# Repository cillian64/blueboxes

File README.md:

# blueboxes
Exciting bass guitar orientated DIY effects pedals

## DI
* DI box for practice with headphones or a consumer hi-fi amp
* Inputs:
    * Unbalanced mono Hi-Z from guitar (TS)
    * Unbalanced stereo line-level backing (TRS)
* Outputs:
    * Unbalanced stereo line-level to amp (RCA)
    * Unbalanced stereo headphone-level (TRS)
* Controls:
    * Instrument volume (mono logpot)
    * Output volume (stereo logpot)
    * on/off switch
* Inside:
    * Hi-Z opamp with gain control for instrument
    * dual op-amp buffer on instrument
    * summing network into stereo opamp outputs

## DSP
* Platform for custom DSP effects
* Inputs:
    * Unbalanced mono hi-Z from guitar (TS)
* Outputs:
    * Unbalanced mono (TS)
* Controls:
    * Rotary encoder with push
    * 4-digit 7-seg LED
    * Stomp-switch for on/thru

## Silly Fuzz
* Simple silicon clone of Fuzz-Face
* Inputs:
    * Unbalanced mono hi-Z from guitar (TS)
* Outputs:
    * Unbalanced mono (TS)
* Controls:
    * Stomp-switch for on/thru
    * Volume log-pot
    * Fuzz-level pot

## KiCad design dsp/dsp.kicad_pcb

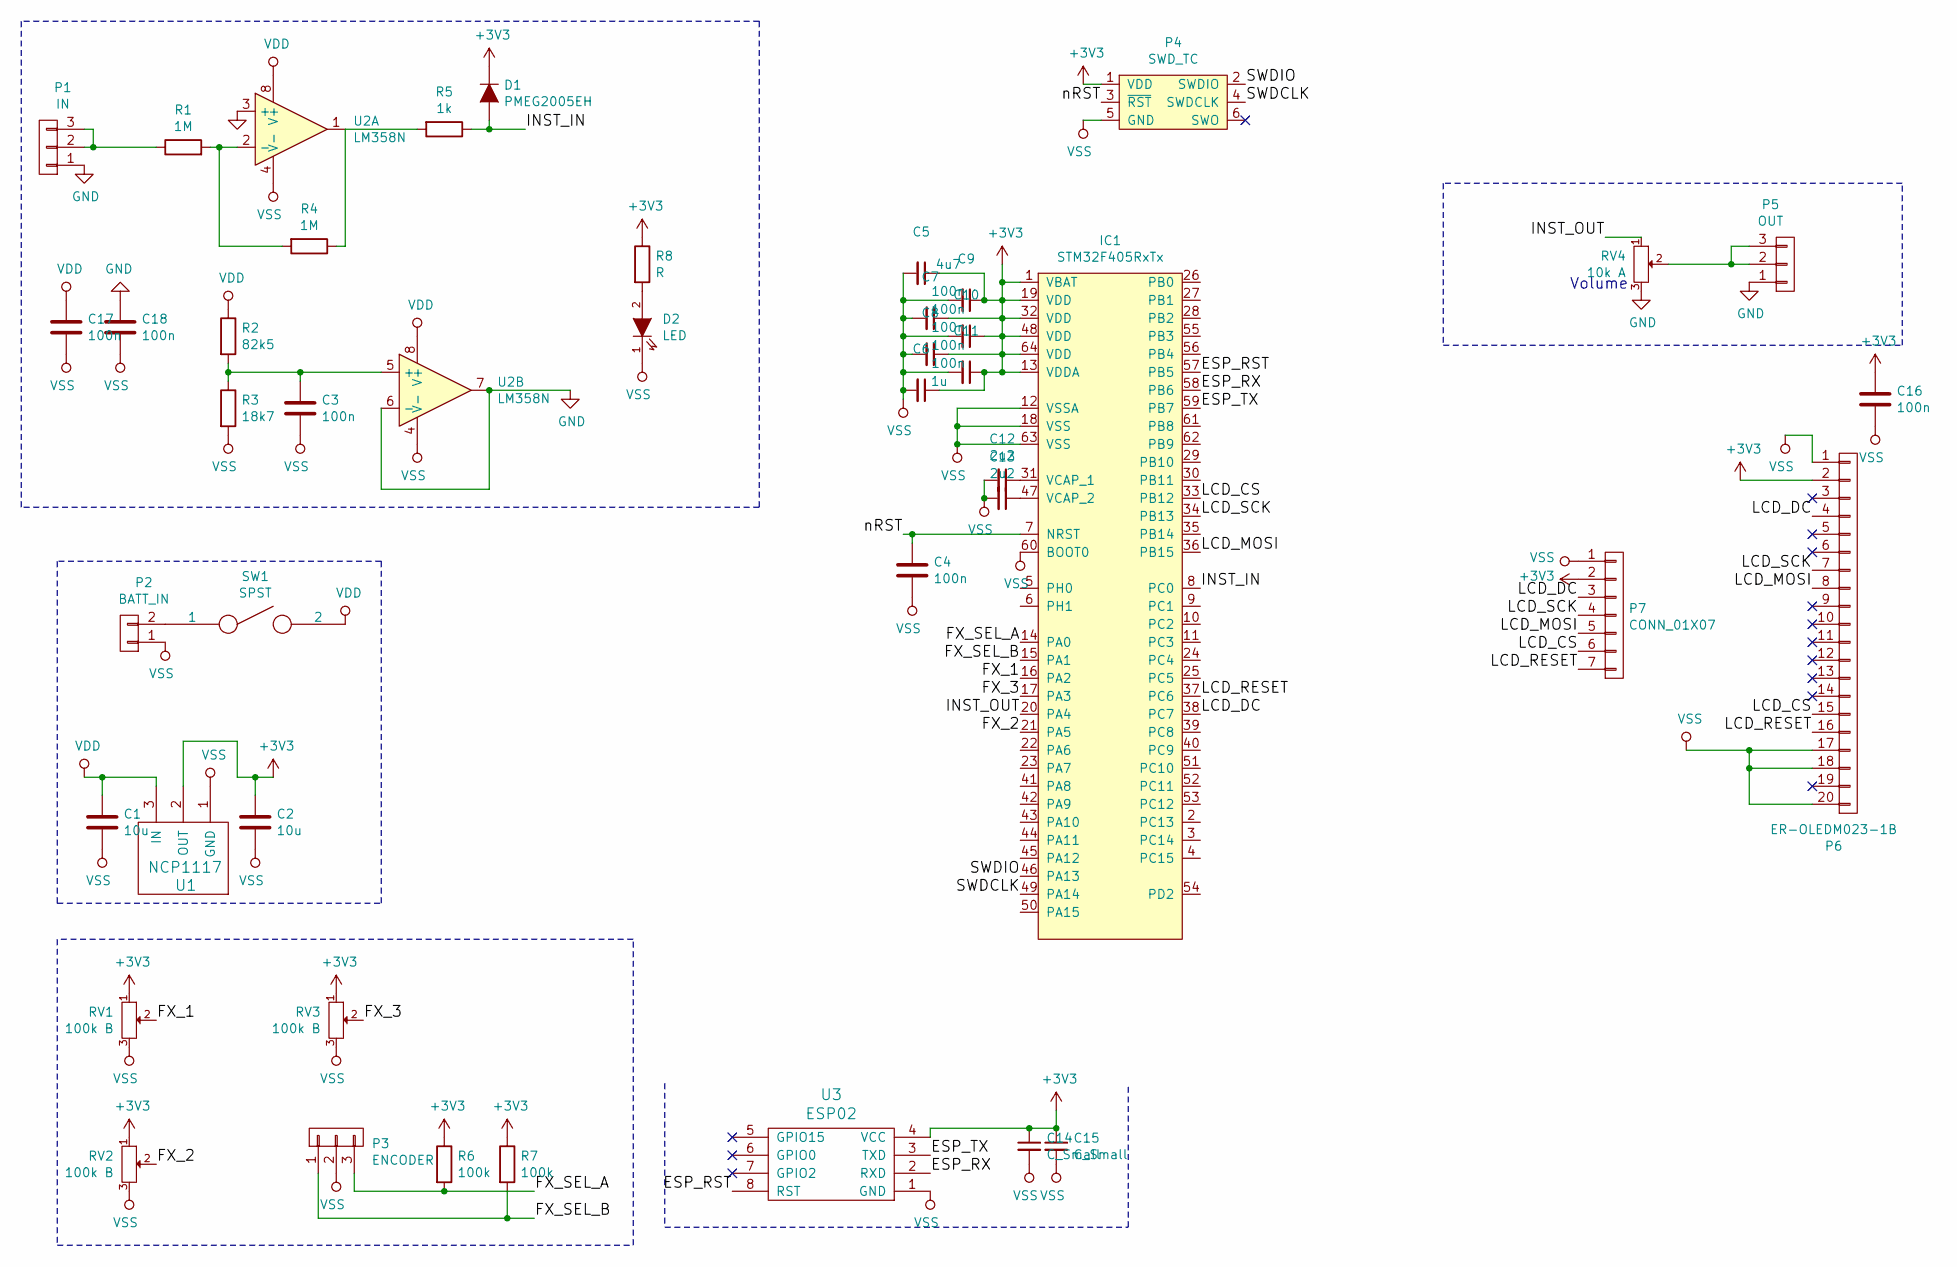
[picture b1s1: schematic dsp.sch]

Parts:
C1, C2: 10u; 0603
C3, C4, C7, C8, C9, C10, C11, C16, C17, C18: 100n; 0603
C5: 4u7; 0603
C6: 1u; 0603
C12, C13: 2u2; 0603
C14: C_Small; 0603
C15: C_Small; 1210
D1: PMEG2005EH; SOD-123F
D2: LED; Pin_Header_Straight_1x02
IC1: STM32F405RxTx; LQFP-64; Farnell 2064363
P1: IN; Pin_Header_Straight_1x03
P2: BATT_IN; Pin_Header_Straight_1x02
P3: ENCODER; Pin_Header_Straight_1x03
P4: SWD_TC; TC2030-NL
P5: OUT; Pin_Header_Straight_1x03
P6: ER-OLEDM023-1B
P7: CONN_01X07; Pin_Header_Straight_1x07
R1, R4: 1M; 0603
R2: 82k5; 0603
R3: 18k7; 0603
R5: 1k; 0603
R6, R7: 100k; 0603
R8: R; 0603
RV1, RV2, RV3: 100k B; Pin_Header_Straight_1x03
RV4: 10k A; Pin_Header_Straight_1x03
SW1: SPST; Pin_Header_Straight_1x02
U1: NCP1117; TO-252-2Lead
U2: LM358N; SOIC-8
U3: ESP02; esp02

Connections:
+3V3: C2.1, C5.1, C6.1, C7.1, C8.1, C9.1, C10.1, C11.1, C14.1, C15.1, C16.1, D1.1 (K), IC1.1 (VBAT), IC1.13 (VDDA), IC1.19 (VDD), IC1.32 (VDD), IC1.48 (VDD), IC1.64 (VDD), P4.1 (VDD), P6.2, P7.2, R6.1, R7.1, R8.1, RV1.1, RV2.1, RV3.1, U1.2 (OUT), U3.4 (VCC)
/ESP_RST: IC1.57 (PB5), U3.8 (RST)
/ESP_RX: IC1.58 (PB6), U3.2 (RXD)
/ESP_TX: IC1.59 (PB7), U3.3 (TXD)
/FX_1: IC1.16 (PA2), RV1.2
/FX_2: IC1.21 (PA5), RV2.2
/FX_3: IC1.17 (PA3), RV3.2
/FX_SEL_A: IC1.14 (PA0), P3.3, R6.2
/FX_SEL_B: IC1.15 (PA1), P3.1, R7.2
/INST_IN: D1.2 (A), IC1.8 (PC0), R5.1
/INST_OUT: IC1.20 (PA4), RV4.1
/LCD_CS: IC1.33 (PB12), P6.15, P7.6
/LCD_DC: IC1.38 (PC7), P6.4, P7.3
/LCD_MOSI: IC1.36 (PB15), P6.8, P7.5
/LCD_RESET: IC1.37 (PC6), P6.16, P7.7
/LCD_SCK: IC1.34 (PB13), P6.7, P7.4
/SWDCLK: IC1.49 (PA14), P4.4 (SWDCLK)
/SWDIO: IC1.46 (PA13), P4.2 (SWDIO)
/nRST: C4.1, IC1.7 (NRST), P4.3 (~RST)
GND: C18.1, P1.1, P5.1, RV4.3, U2.3 (+), U2.6 (-), U2.7
unnamed: C3.1, R2.2, R3.1, U2.5 (+)
unnamed: C12.1, IC1.31 (VCAP_1)
unnamed: C13.1, IC1.47 (VCAP_2)
unnamed: D2.2 (A), R8.2
unnamed: P1.2, P1.3, R1.1
unnamed: P2.2, SW1.1
unnamed: P5.2, P5.3, RV4.2
unnamed: R1.2, R4.2, U2.2 (-)
unnamed: R4.1, R5.2, U2.1
VDD: C1.1, C17.1, R2.1, SW1.2, U1.3 (IN), U2.8 (V+)
VSS: C1.2, C2.2, C3.2, C4.2, C5.2, C6.2, C7.2, C8.2, C9.2, C10.2, C11.2, C12.2, C13.2, C14.2, C15.2, C16.2, C17.2, C18.2, D2.1 (K), IC1.12 (VSSA), IC1.18 (VSS), IC1.60 (BOOT0), IC1.63 (VSS), P2.1, P3.2, P4.5 (GND), P6.1, P6.17, P6.18, P6.20, P7.1, R3.2, RV1.3, RV2.3, RV3.3, U1.1 (GND), U2.4 (V-), U3.1 (GND)

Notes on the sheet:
Volume

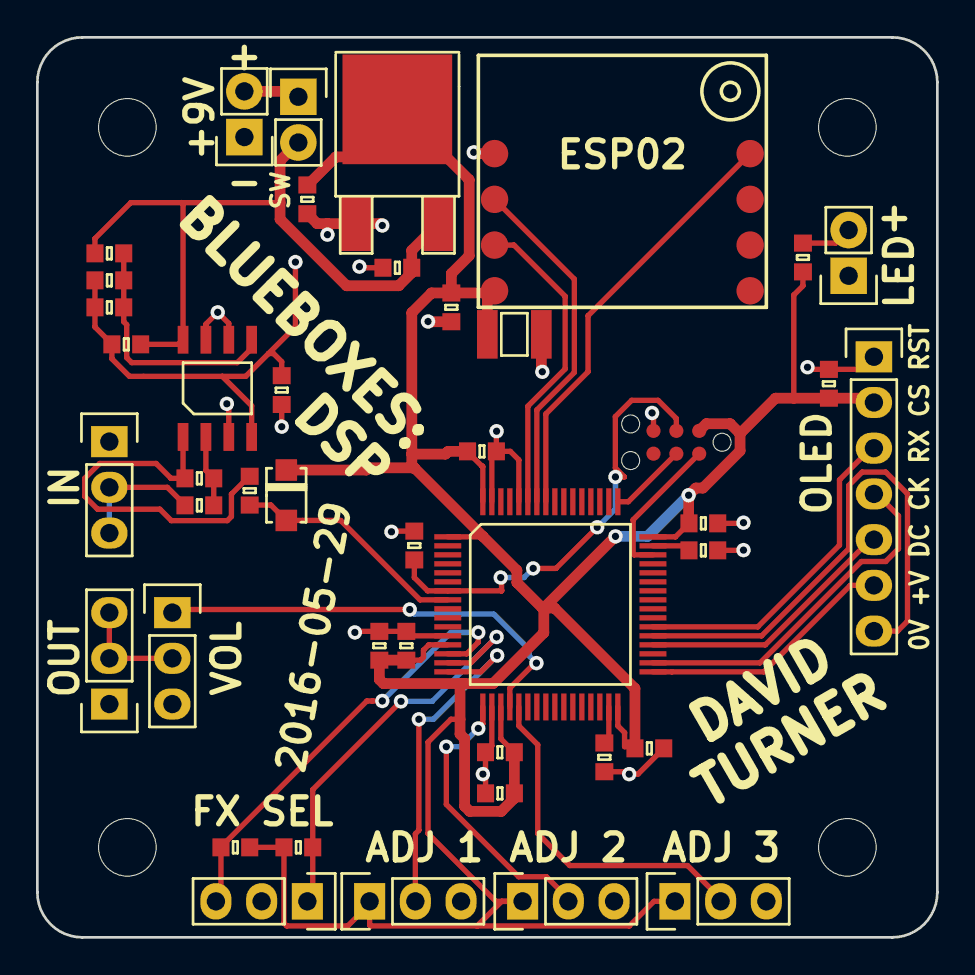
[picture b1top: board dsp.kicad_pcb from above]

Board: 2 copper layers, 50.0 x 50.0 mm, 43 parts (0 on the bottom side), 31 nets.

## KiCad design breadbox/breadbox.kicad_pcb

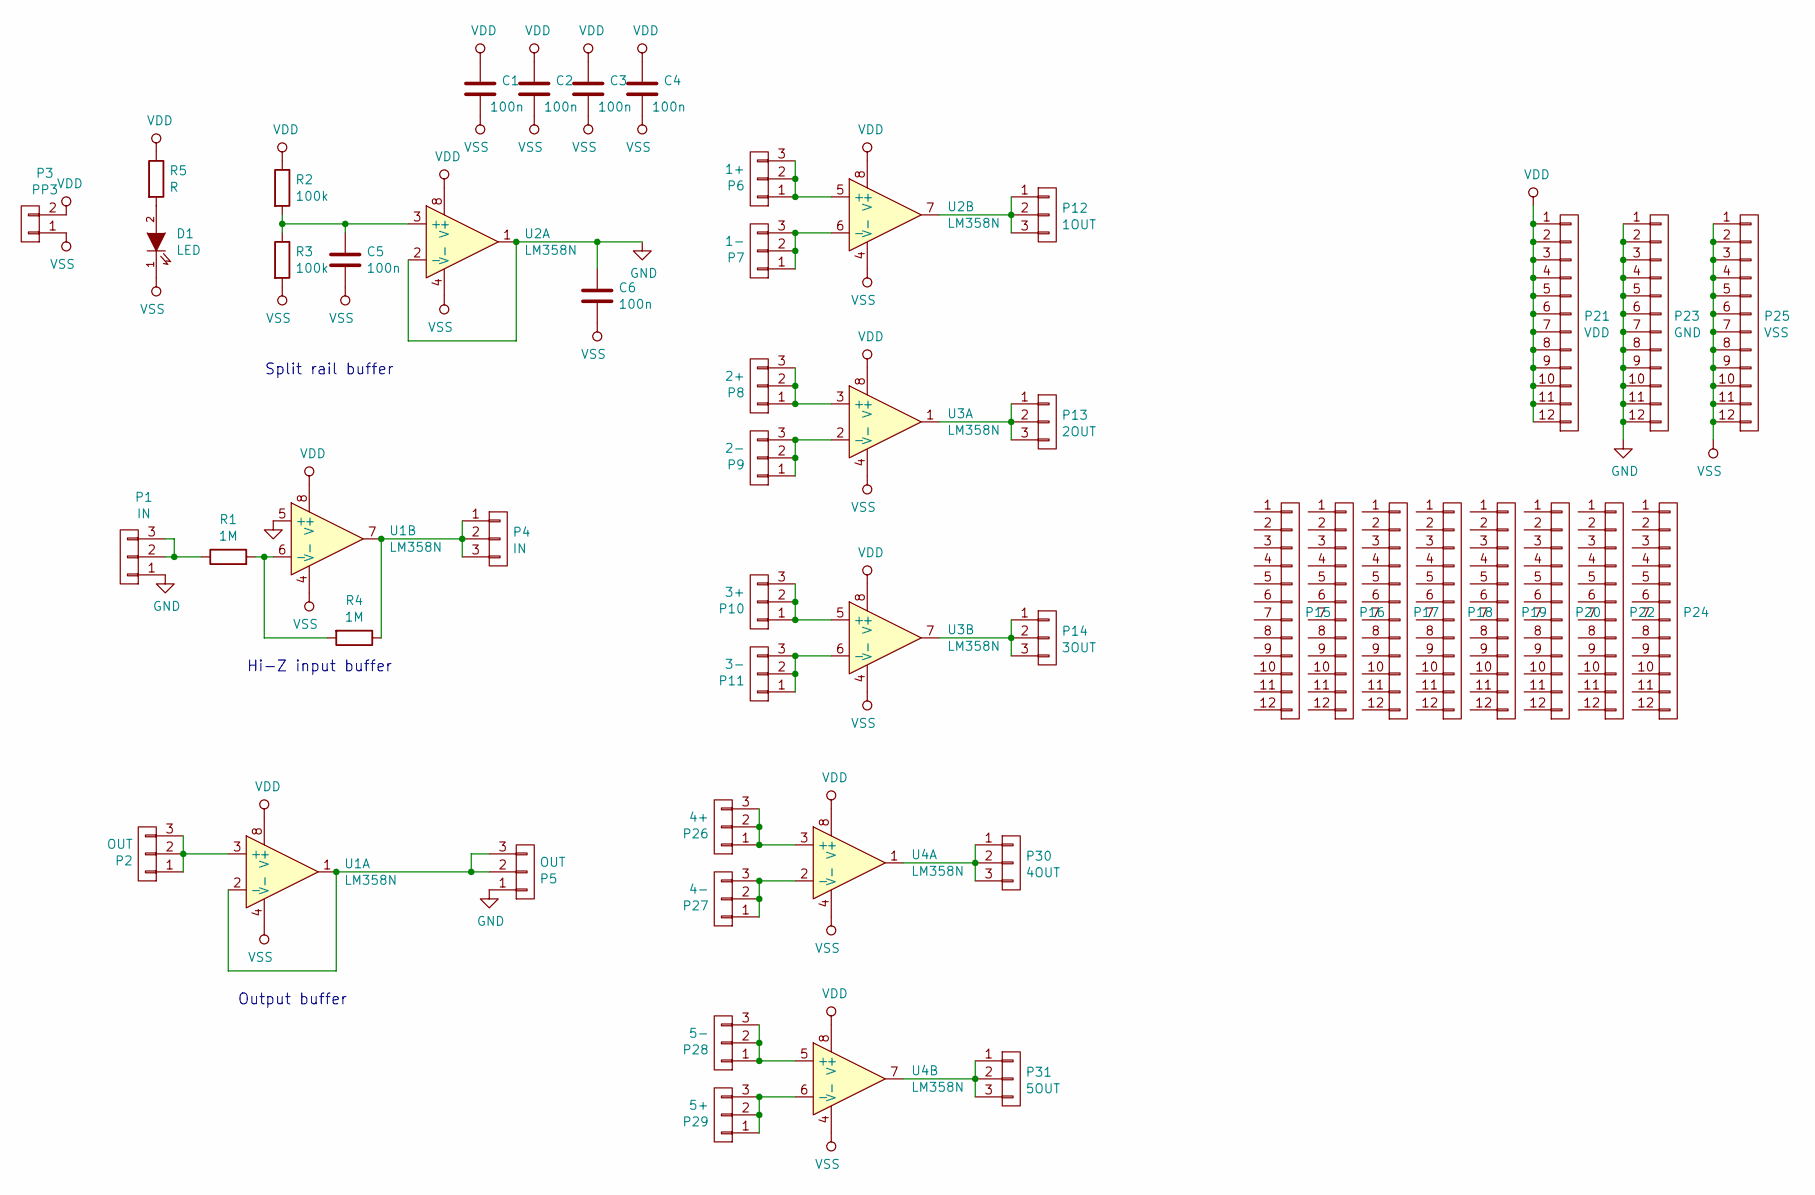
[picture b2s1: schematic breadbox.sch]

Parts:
C1, C2, C3, C4, C5: 100n; C_0603
C6: 100n; 0603
D1: LED; Pin_Header_Straight_1x02
P1, P4: IN; Pin_Header_Straight_1x03
P2, P5: OUT; Pin_Header_Straight_1x03
P3: PP3; Pin_Header_Straight_1x02
P6: 1+; Pin_Header_Straight_1x03
P7: 1-; Pin_Header_Straight_1x03
P8: 2+; Pin_Header_Straight_1x03
P9: 2-; Pin_Header_Straight_1x03
P10: 3+; Pin_Header_Straight_1x03
P11: 3-; Pin_Header_Straight_1x03
P12: 1OUT; Pin_Header_Straight_1x03
P13: 2OUT; Pin_Header_Straight_1x03
P14: 3OUT; Pin_Header_Straight_1x03
P15, P16, P17, P18, P19, P20, P22, P24: CONN; Pin_Header_Straight_1x12
P21: VDD; Pin_Header_Straight_1x12
P23: GND; Pin_Header_Straight_1x12
P25: VSS; Pin_Header_Straight_1x12
P26: 4+; Pin_Header_Straight_1x03
P27: 4-; Pin_Header_Straight_1x03
P28: 5-; Pin_Header_Straight_1x03
P29: 5+; Pin_Header_Straight_1x03
P30: 4OUT; Pin_Header_Straight_1x03
P31: 5OUT; Pin_Header_Straight_1x03
R1, R4: 1M; R_0603
R2, R3: 100k; R_0603
R5: R; 0603
U1, U2, U3, U4: LM358N; SOIC-8_3.9x4.9mm_Pitch1.27mm

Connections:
GND: C6.1, P1.1, P5.1, P23.1, P23.2, P23.3, P23.4, P23.5, P23.6, P23.7, P23.8, P23.9, P23.10, P23.11, P23.12, U1.5 (+), U2.1, U2.2 (-)
unnamed: C5.1, R2.2, R3.1, U2.3 (+)
unnamed: D1.2 (A), R5.2
unnamed: P1.2, P1.3, R1.1
unnamed: P2.1, P2.2, P2.3, U1.3 (+)
unnamed: P4.1, P4.2, P4.3, R4.1, U1.7
unnamed: P5.2, P5.3, U1.1, U1.2 (-)
unnamed: P6.1, P6.2, P6.3, U2.5 (+)
unnamed: P7.1, P7.2, P7.3, U2.6 (-)
unnamed: P8.1, P8.2, P8.3, U3.3 (+)
unnamed: P9.1, P9.2, P9.3, U3.2 (-)
unnamed: P10.1, P10.2, P10.3, U3.5 (+)
unnamed: P11.1, P11.2, P11.3, U3.6 (-)
unnamed: P12.1, P12.2, P12.3, U2.7
unnamed: P13.1, P13.2, P13.3, U3.1
unnamed: P14.1, P14.2, P14.3, U3.7
unnamed: P26.1, P26.2, P26.3, U4.3 (+)
unnamed: P27.1, P27.2, P27.3, U4.2 (-)
unnamed: P28.1, P28.2, P28.3, U4.5 (+)
unnamed: P29.1, P29.2, P29.3, U4.6 (-)
unnamed: P30.1, P30.2, P30.3, U4.1
unnamed: P31.1, P31.2, P31.3, U4.7
unnamed: R1.2, R4.2, U1.6 (-)
VDD: C1.1, C2.1, C3.1, C4.1, P3.2, P21.1, P21.2, P21.3, P21.4, P21.5, P21.6, P21.7, P21.8, P21.9, P21.10, P21.11, P21.12, R2.1, R5.1, U1.8 (V+), U2.8 (V+), U3.8 (V+), U4.8 (V+)
VSS: C1.2, C2.2, C3.2, C4.2, C5.2, C6.2, D1.1 (K), P3.1, P25.1, P25.2, P25.3, P25.4, P25.5, P25.6, P25.7, P25.8, P25.9, P25.10, P25.11, P25.12, R3.2, U1.4 (V-), U2.4 (V-), U3.4 (V-), U4.4 (V-)

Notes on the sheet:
Split rail buffer
Hi-Z input buffer
Output buffer

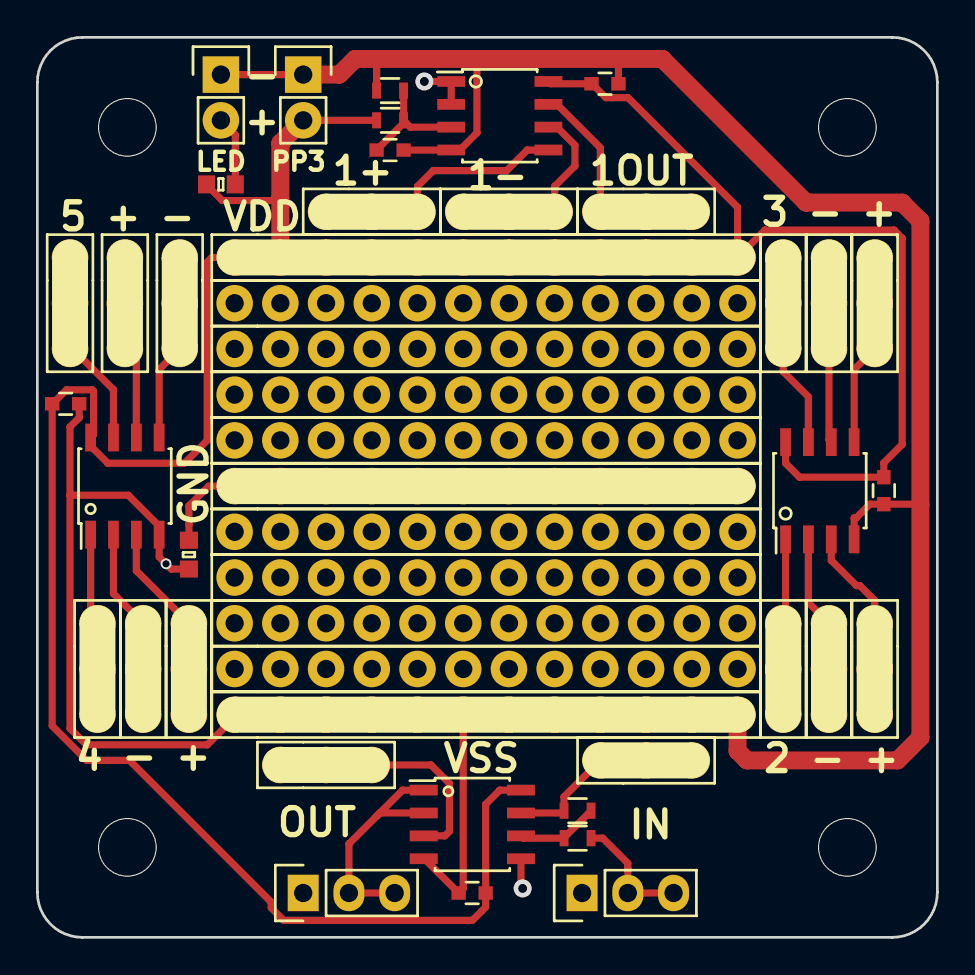
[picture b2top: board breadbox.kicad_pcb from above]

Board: 2 copper layers, 50.0 x 50.0 mm, 47 parts (0 on the bottom side), 25 nets.

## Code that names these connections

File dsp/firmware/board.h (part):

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/*
 * GPIOA setup:
 *
 * PA0  - FX_SEL_A                  (alternate 1).
 * PA1  - FX_SEL_B                  (alternate 1).
 * PA2  - FX_1                      (analog).
 * PA3  - FX_3                      (analog).
 * PA4  - INST_OUT                  (analog).
 * PA5  - FX_2                      (analog).
 * PA6  - PIN6                      (input pullup).
 * PA7  - PIN7                      (input pullup).
 * PA8  - PIN8                      (input pullup).
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 * PA10 - PIN10                     (input pullup).
 * PA11 - PIN11                     (input pullup).
 * PA12 - PIN12                     (input pullup).
 * PA13 - SWDIO                     (alternate 0).
 * PA14 - SWCLK                     (alternate 0).
 * PA15 - PIN15                     (input pullup).
 */
#define VAL_GPIOA_MODER             (PIN_MODE_ALTERNATE(GPIOA_FX_SEL_A) |   \
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 * PB2  - PIN2                      (input pullup).
 * PB3  - PIN3                      (input pullup).
 * PB4  - PIN4                      (input pullup).
 * PB5  - ESP_RST                   (output pushpull maximum).
 * PB6  - ESP_RX                    (alternate 7).
 * PB7  - ESP_TX                    (alternate 7).
 * PB8  - PIN8                      (input pullup).
 * PB9  - PIN9                      (input pullup).
 * PB10 - PIN10                     (input pullup).
 * PB11 - PIN11                     (input pullup).
 * PB12 - LCD_CS                    (output pushpull maximum).
 * PB13 - LCD_SCK                   (alternate 5).
 * PB14 - PIN14                     (input pullup).
 * PB15 - LCD_MOSI                  (alternate 5).
 */
#define VAL_GPIOB_MODER             (PIN_MODE_INPUT(GPIOB_PIN0) |           \
                                     PIN_MODE_INPUT(GPIOB_PIN1) |           \
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/*
 * GPIOC setup:
 *
 * PC0  - INST_IN                   (analog).
 * PC1  - PIN1                      (input pullup).
 * PC2  - PIN2                      (input pullup).
 * PC3  - PIN3                      (input pullup).
 * PC4  - PIN4                      (input pullup).
 * PC5  - PIN5                      (input pullup).
 * PC6  - LCD_RESET                 (output pushpull maximum).
 * PC7  - LCD_DC                    (output pushpull maximum).
 * PC8  - PIN8                      (input pullup).
 * PC9  - PIN9                      (input pullup).
 * PC10 - PIN10                     (input pullup).
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
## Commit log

2016-05-24 Initial commit of sillyfuzz and di
2016-05-24 Started on DSP schematic
2016-05-24 Added ESP01 to DSPbox
2016-05-26 Higher impedance inst inputs
2016-05-26 Proof-of-concept demo simplified DI box
2016-05-26 di simplified stuff
2016-05-27 Split rails, direct coupled input/output
2016-05-27 schematic fiddling
2016-05-27 Manual diode clipping: Clippy!
2016-05-27 removed coupling from DI
2016-05-27 layout stuff
2016-05-29 Finished Breadbox PCB
2016-05-29 Added C5, changed M3-mount to M3 hole
2016-05-30 Breadbox schematic and finished PCB
2016-05-30 DSP PCB
2016-05-30 Final tweaks
2016-06-03 Added farnell parts, removed unfitted LED
2016-06-03 Breadbox BOM
2016-06-03 Removed 10x gain from DI box
2016-06-03 Added parts and bom for DSP
2016-06-03 Improved DI schematic
2016-06-12 ChibiOS skeleton
2016-06-12 Removed PCB backup files from repo
2016-06-12 Added paste stencil DXFs
2016-12-10 Added skeleton ADC code
2016-12-11 Added DAC code
2016-12-12 Enable DAC o/p buffer, fiddle GPTs
2016-12-12 ADC/DAC sample size note
2016-12-13 Added buffer notes
2016-12-17 OLED code!
2017-03-13 dsp analog stuff
2020-05-23 Rename "analogue" driver to "analog"
    In British English "analog" is usually for the technical concept rather than
    "analogue".
2020-05-23 Convert Makefile from DOS to UNIX line endings
2020-05-23 Update copyright headers
    ChibiOS RT is GPL3, so blueboxes dsp's firmware also is. Add an appropriate
    header to the source files. (Leaving the ChibiOS boilerplate with its old
    apache headers from chibios HAL).
    Add proper attribution/blame to Adam Greig for the OLED driver cribbed from
    Supervide.
2020-05-23 Basic ADC demo
    Continuous conversion of a single channel into a single buffer, each sample
    triggered by a (almost) 44kHz timer. Samples look good.
2020-05-23 TIM3 and TIM8 are swapped
    INST ADC and DAC need to use TIM8 because DAC can't trigger off TIM3 TRGO. I
    was confusing TIM3 as inst and TIM8 as FX which is the wrong way around.
2020-05-24 Basic DAC demo
    Output a hard-coded sinusoid waveform to the DAC using a single circular
    buffer.
2020-05-24 Use named member initialisation for config structs
    Also make comments a bit more helpful

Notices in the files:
dsp/firmware/board.h:
ChibiOS - Copyright (C) 2006..2016 Giovanni Di Sirio
Licensed under the Apache License, Version 2.0 (the "License");
